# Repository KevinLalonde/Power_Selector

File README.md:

# Power_Selector
Ce circuit permet de pouvoir sélectionner quelle alimentation est envoyée au drone entre l'alimentation du sol et l'alimentation de la batterie

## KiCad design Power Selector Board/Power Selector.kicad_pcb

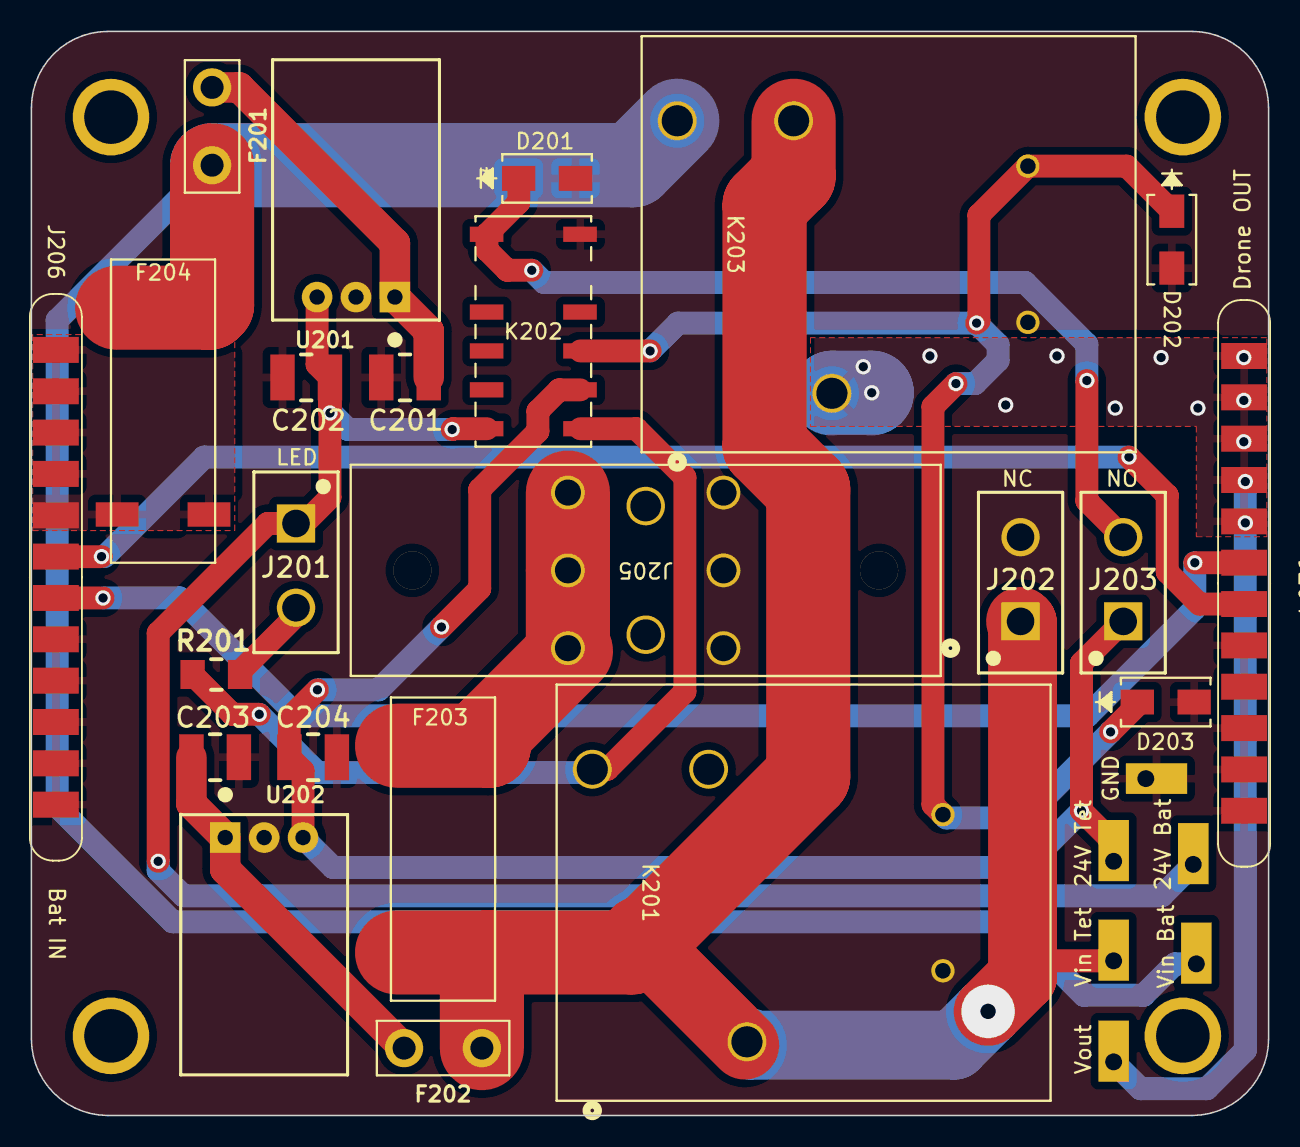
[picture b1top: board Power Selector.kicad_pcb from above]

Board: 2 copper layers, 80.8 x 70.8 mm, 33 parts (0 on the bottom side), 16 nets.

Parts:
C201, C202, C203, C204: GRM32EC72A106ME05L; C1210
D201, D202, D203: S1D-13-F; SMA_DIO
F201, F202: 0698Q2000-02; TE5_395
F203, F204: 047706.3MRET1P; 3587TR
H1, H2, H3, H4: Mounting-Hole-M3; Mounting_Hole_3mm
J201, J202, J203: 64900221122
J204: MSD-DB01M-12P; MSD-DB01F-12P-V2.0
J205: 1998865
J206: MSD-DB01F-12P_1; MSD-DB01F-12P-V2.0
K201, K203: J115F11C24VDCSH.9; RELAY5_J115F11C24VDCSH.9_CRS
K202: G6SK-2G DC24; G6SK-2G DC3_OMR
R201: RC1206JR-07120RL; R1206
TP1: Vin Bat; Keystone_5001
TP2: 24V Bat; Keystone_5001
TP3: Vin Tether; Keystone_5001
TP4: 24V Tether; Keystone_5001
TP5: GND; Keystone_5001
TP6: Vout Drone; Keystone_5001
U201, U202: LMW78_24-0.3RL; OKI-78SR_Horizontal

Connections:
24V_Bat_G: C202.2, J201.1, K202.6, TP2.1 (TP), U201.3 (Vout)
24V_Tether_G: C204.2, J203.1, K202.8, TP4.1 (TP), U202.3 (Vout)
+Vin_Drone_G: J204.1, J204.2, J204.3, J204.4, J204.5, K203.3, TP6.1 (TP)
+Vin_Tether_G: F202.1, F203.1, J202.1, K201.3, K203.2, TP3.1 (TP)
/PCB_Gauche/Relay_Active: D202.1, D203.1, K201.4, K202.9, K203.4
/PCB_Gauche/SCL: J204.6, J206.7
/PCB_Gauche/SDA: J204.7, J206.6
GND_G: C201.1, C202.1, C203.1, C204.1, D201.2, D202.2, D203.2, J202.2, J204.8, J204.9, J204.10, J204.11, J204.12, J205.1, J205.2, J205.3, J206.8, J206.9, J206.10, J206.11, J206.12, K201.5, K202.12, K203.5, TP5.1 (TP), U201.2 (GND), U202.2 (GND)
unnamed: D201.1, J203.2, K202.1
unnamed: F203.2, J205.4, J205.5, J205.6
unnamed: F204.2, J206.1, J206.2, J206.3, J206.4, J206.5
unnamed: J201.2, R201.2
unnamed: K201.1, K202.7, R201.1
unnamed: C201.2, F201.2, U201.1 (Vin)
unnamed: C203.2, F202.2, U202.1 (Vin)
Vin_Bat_G: F201.1, F204.1, K203.1, TP1.1 (TP)

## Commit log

2023-07-17 Ajout du projet KiCad et ded la librairie
2023-07-17 Ajout symbole MSD-DB01F-12P-V2.0 dans la librairy
2023-07-18 Ajout symbole et debut footprint MSD-DB01F-12P-V2.0 dans la librairy
2023-07-18 Ajout d'un connecteur
2023-07-19 Ré-ajout de la librairie
2023-07-19 Ajout du connecteur male
2023-07-19 Ajout de tous les connecteurs
2023-07-19 Changements mineurs aux connections des connecteurs
2023-07-21 Ajout connecteur batterie drone femelle MSD-DB01F-12P-V2.0
2023-07-21 Ajout d'un relais et completion du circuit de controle
2023-07-21 Clarification de la schematic, ajout de commentaires
2023-07-23 Ajout du circuit de la tension de controle
2023-07-23 Finalisation du schema, en atttente d'un design review, PCB pret a commencer a etre routé
2023-07-23 Update footprint connecteur batterie/drone
2023-07-24 Debut routing
2023-07-24 Fix du bug github, devrait etre la bonne version
2023-07-24 Ajout des deux PCB (droit et gauche) sur le meme PCB
2023-07-24 Premier commit pour routing PCB. Modif footprint connecteur batterie.
2023-07-25 Routing PCB gauche. Prêt pour review 1.
2023-07-25 Ajout testpoints au schéma et PCB. Ajout de commentaires sur le silkscreen.
2023-07-26 Fix region fills, add missing scl/sda traces & fix pad connections
2023-08-01 Modif apportées à la grosseur des trous minimum pour respecter les contraintes de fabrication de l'ÉTS. Aucune erreur de DRC, seulement des warnings de silkscreen qui overlap, not an issue.
2023-08-22 Ajout rapports finaux.
